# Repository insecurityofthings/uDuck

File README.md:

# μDuck

μDuck is a stealth HID injector. It's a very small USB device that acts like a scripted keyboard. This can be used for automation and lulz, and has obvious security implications. It's quite similar  to the [Hak5 Rubber Ducky](https://hakshop.com/products/usb-rubber-ducky-deluxe) in terms of functionality, and even uses the [same syntax](https://github.com/hak5darren/USB-Rubber-Ducky/wiki/Payloads) to define the scripted input.

When μDuck is connected, it will wait for 2 seconds in programming mode before switching to a keyboard. This allows the payload to be updated with the Python tool provided. It will wait for 5 seconds before the first HID injection, then retry the payload automatically at 60 seconds, 5 minutes, and then every 4 hours with +/- 1 hour of random variance. This ensures reliable delivery, but expect that your payload may run more than once.

## Building a μDuck

The μDuck is quite inexpensive -- all the parts cost around $2 per unit. However, you will need some tools and know-how to get started. For more information, see the README file in the doc directory.

## Credits and License

The hardware is borrowed from [this blog](http://www.morethantechnical.com/2015/08/03/smallest-attiny45-usb/). The software is a modified version of "CapsLocker", which can be [found here](http://macetech.com/blog/?q=node/46). Our customized hardware design can be found in the "hardware" folder.

Our Python code and hardware design is MIT licensed. The USB firmware is licensed [according to the terms](https://www.obdev.at/products/vusb/license.html) of Objective Development's vUSB and GPLv2.

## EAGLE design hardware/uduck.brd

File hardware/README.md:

Fixes
=====

- Schematic shows a 2k resistor. Use 1.5k instead.
- See [the documentation](https://github.com/phikshun/uDuck/tree/master/doc) for suggested parts.

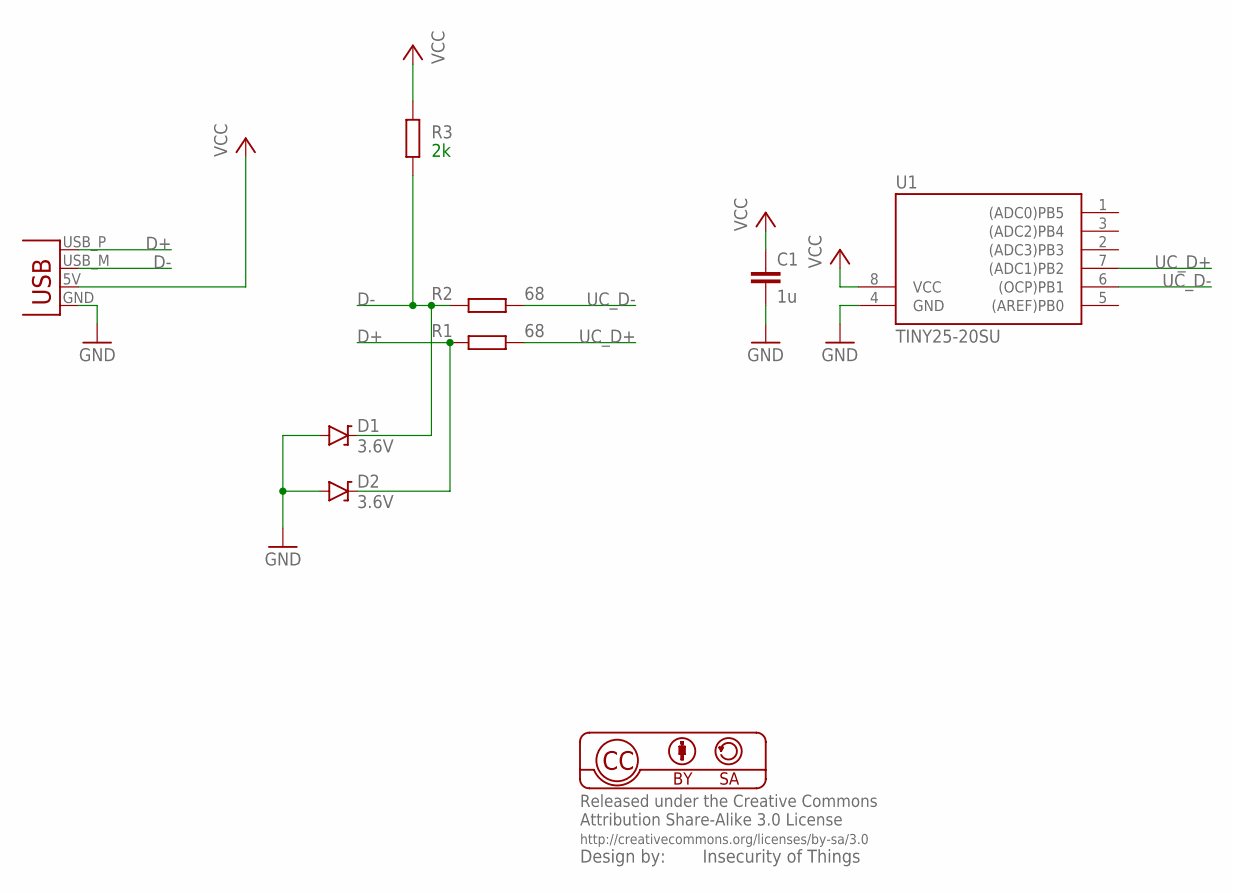
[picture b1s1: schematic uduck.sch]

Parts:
C1: 1u; C0805
D1, D2: 3.6V; SOD-323
R1, R2: 68; R0603
R3: 2k; R0603
U1: TINY25-20SU; SOIC8
X1: USBPCB; USB-A-PCB

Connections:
D+: D2.C, R1.2, X1.USB_P (D+)
D-: D1.C, R2.2, R3.1, X1.USB_M (D-)
GND: C1.2, D1.A, D2.A, U1.4 (GND), X1.GND
UC_D+: R1.1, U1.7 ((ADC1)PB2)
UC_D-: R2.1, U1.6 ((OCP)PB1)
VCC: C1.1, R3.2, U1.8 (VCC), X1.5V (VBUS)

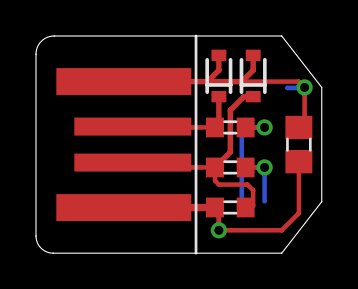
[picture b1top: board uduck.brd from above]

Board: 2 copper layers, 15.9 x 12.1 mm, 8 parts (1 on the bottom side), 6 nets.

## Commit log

2016-10-16 added backoff delays
2016-11-04 Added hardware design
2016-11-04 modified README
2016-11-07 added python programming tool for micronucleus bootloader
2016-11-08 restructured project files
2016-11-08 Added build instructions
2016-12-04 fixed patching
2016-12-04 Added comments

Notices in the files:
parts and their libraries:
SparkFun-DiscreteSemi: Licensing: Creative Commons ShareAlike 4.0 International - https://creativecommons.org/licenses/by-sa/4.0
balto: Released under the Creative Commons
balto: http://creativecommons.org/licenses/by-sa/3.0
